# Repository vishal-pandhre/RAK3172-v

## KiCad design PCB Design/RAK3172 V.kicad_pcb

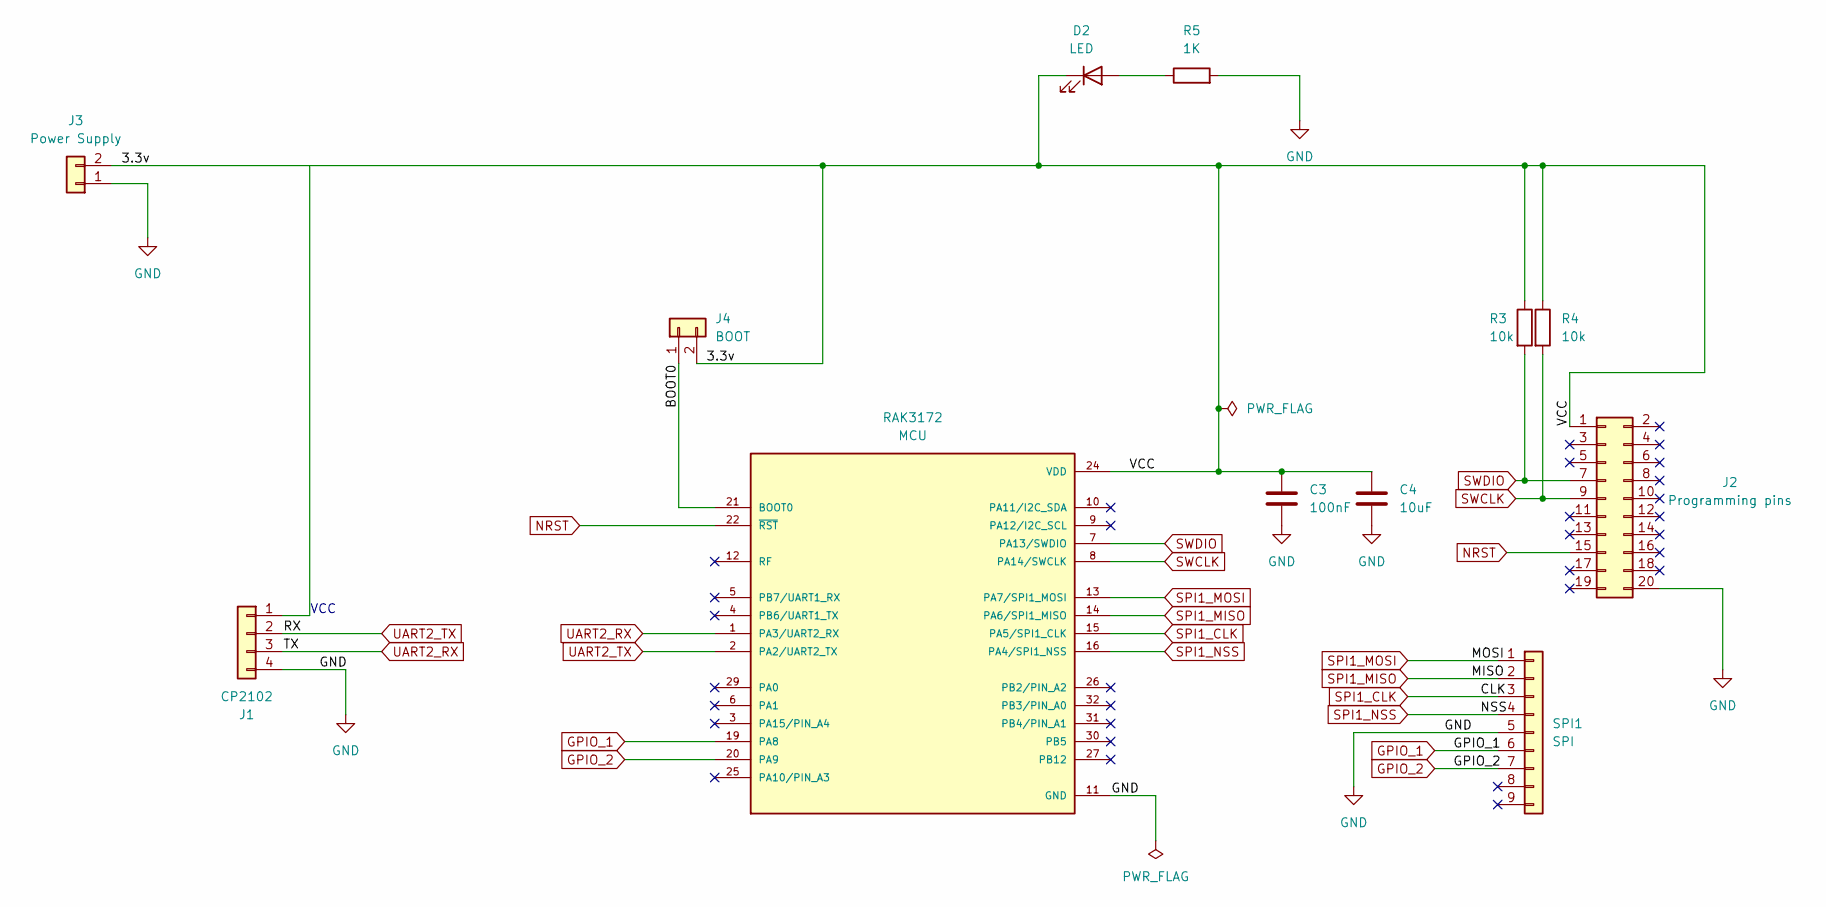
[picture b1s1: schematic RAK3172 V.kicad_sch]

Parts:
C3: 100nF; C_1206_3216Metric
C4: 10uF; C_1206_3216Metric
D2: LED; LED_0805_2012Metric
J1: CP2102; PinHeader_1x04_P2.54mm_Vertical
J2: Programming pins; PinHeader_2x10_P2.54mm_Vertical
J3: Power Supply; PinHeader_1x02_P2.54mm_Vertical
J4: BOOT; PinHeader_1x02_P2.54mm_Vertical
R3, R4: 10k; R_1206_3216Metric
R5: 1K; R_0805_2012Metric
RAK3172: MCU; RAK3172; PARTREV 20/02/2026
SPI1: SPI; PinHeader_1x09_P2.54mm_Vertical

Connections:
/3.3v: C3.1, C4.1, D2.1 (K), J1.1, J2.1, J3.2, J4.2, R3.1, R4.1, RAK3172.24 (VDD)
/BOOT0: J4.1, RAK3172.21 (BOOT0)
GND: C3.2, C4.2, J1.4, J2.20, J3.1, R5.2, RAK3172.11 (GND), RAK3172.17 (GND), RAK3172.18 (GND), RAK3172.23 (GND), RAK3172.28 (GND), SPI1.5
GPIO_1: RAK3172.19 (PA8), SPI1.6
GPIO_2: RAK3172.20 (PA9), SPI1.7
NRST: J2.15, RAK3172.22 (~RST)
unnamed: D2.2 (A), R5.1
SPI1_CLK: RAK3172.15 (PA5/SPI1_CLK), SPI1.3
SPI1_MISO: RAK3172.14 (PA6/SPI1_MISO), SPI1.2
SPI1_MOSI: RAK3172.13 (PA7/SPI1_MOSI), SPI1.1
SPI1_NSS: RAK3172.16 (PA4/SPI1_NSS), SPI1.4
SWCLK: J2.9, R4.2, RAK3172.8 (PA14/SWCLK)
SWDIO: J2.7, R3.2, RAK3172.7 (PA13/SWDIO)
UART2_RX: J1.3, RAK3172.1 (PA3/UART2_RX)
UART2_TX: J1.2, RAK3172.2 (PA2/UART2_TX)

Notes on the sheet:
VCC

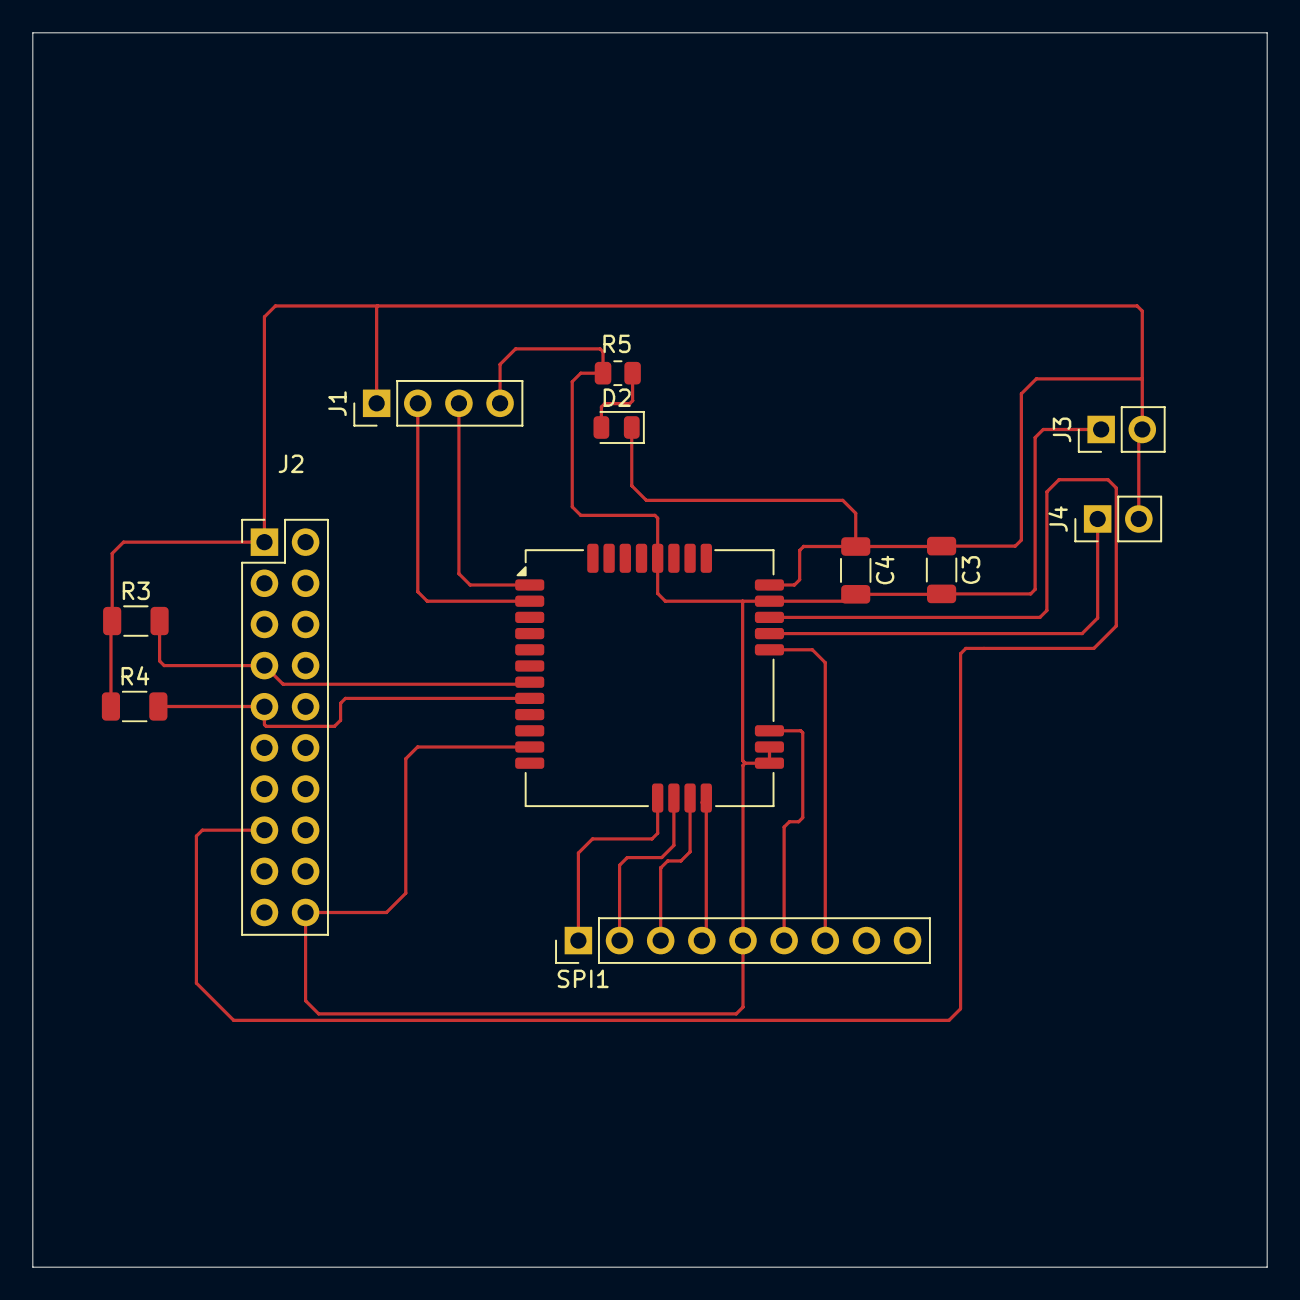
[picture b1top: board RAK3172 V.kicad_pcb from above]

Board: 2 copper layers, 76.2 x 76.2 mm, 12 parts (0 on the bottom side), 15 nets.
